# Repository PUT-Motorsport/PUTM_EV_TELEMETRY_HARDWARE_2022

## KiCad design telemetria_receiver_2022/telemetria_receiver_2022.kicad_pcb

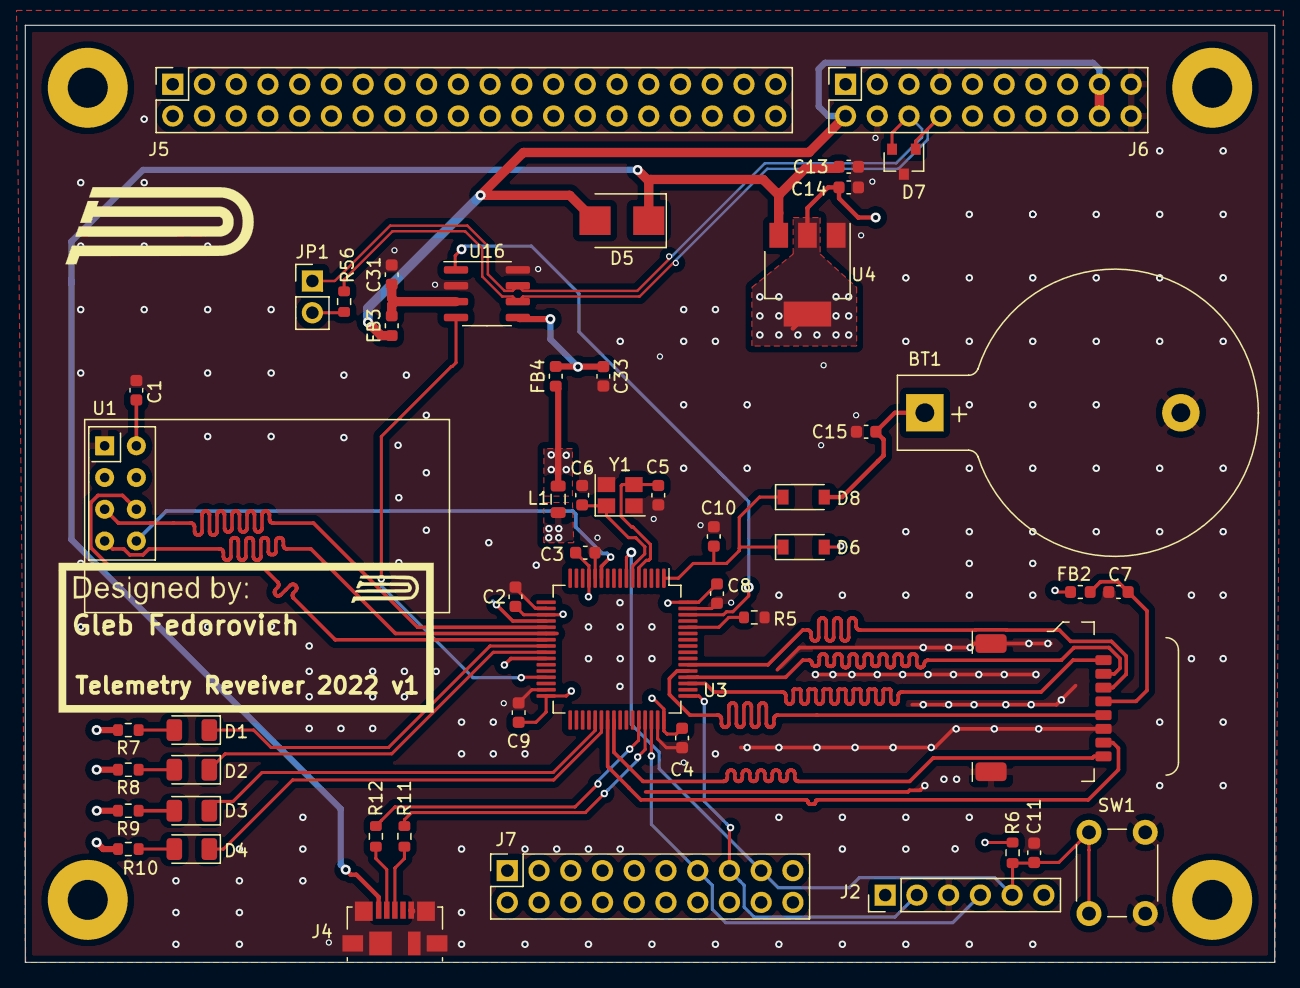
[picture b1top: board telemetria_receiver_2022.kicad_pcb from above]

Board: 4 copper layers, 100.0 x 75.0 mm, 55 parts (0 on the bottom side), 45 nets.

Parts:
BT1: 3V; BatteryHolder_Keystone_103_1x20mm
C1: 10uF; C_0603_1608Metric
C2, C3, C4, C8, C9, C10, C11, C13, C14, C15, C31, C33: 100nF; C_0603_1608Metric
C5, C6: 22pF; C_0603_1608Metric
C7: 4u7F; C_0603_1608Metric
D1, D2, D3, D4: LED; LED_1206_3216Metric
D5: D_Schottky; D_SMB
D6, D8: D_Schottky; D_SOD-123
D7: PESD2CAN.215; SOT-23
FB2, FB3, FB4: 60R@100MHz; L_0603_1608Metric
H1, H2, H3, H4: MountingHole; MountingHole_3.2mm_M3_Pad
J1: Micro_SD_Card; 112K-TAA0-RA1
J2: Conn_01x06_Male; PinHeader_1x06_P2.54mm_Vertical
J4: USB_B_Mini; USB_Micro-B_Molex_47346-0001
J5: Sygnały; PinSocket_2x20_P2.54mm_Vertical
J6: Zasilanie+CAN; PinSocket_2x10_P2.54mm_Vertical
J7: Diagnostyka; PinSocket_2x10_P2.54mm_Vertical
JP1: CAN_termination_jumper; PinHeader_1x02_P2.54mm_Vertical
L1: 10uH; L_0805_2012Metric
R5, R6: 100kR; R_0603_1608Metric
R7, R8, R9, R10: 470R; R_0603_1608Metric
R11, R12: 30R; R_0603_1608Metric
R56: 120R; R_0603_1608Metric
SW1: SW_Push; SW_PUSH_6mm
U1: NRF24L01_Breakout; nRF24L01_Breakout
U3: STM32L4P5RET6; LQFP-64_10x10mm_P0.5mm
U4: LM1117-3.3; SOT-223-3_TabPin2
U16: ATA6561-GAQW-N; SOIC-8_3.9x4.9mm_P1.27mm
Y1: Crystal(100MHZ)?; Crystal_SMD_3225-4Pin_3.2x2.5mm

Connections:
+3V3: C1.1, C14.1, D6.2, FB2.1, FB4.1, J2.1, L1.1, R6.2, R7.2, R8.2, R9.2, R10.2, U1.2, U4.2
+5V: D5.2, FB3.1, J6.2, J6.17, J6.18
+5VD: C13.1, D5.1, J4.1, U4.3
+BATT: BT1.1, C15.2, D8.2
/+3V3_Vbatt: C10.1, D6.1, D8.1, U3.1
/+3V3_uC: C2.1, C3.1, C4.1, C8.1, C9.1, L1.2, U3.13, U3.19, U3.32, U3.48, U3.64
/CAN+: D7.2, J6.6, JP1.1, U16.7
/CAN-: D7.1, J6.8, R56.2, U16.6
/CAN/+3V3_VIO: C33.1, FB4.2, U16.5
/CAN/+5V_CAN_VDD: C31.1, FB3.2, U16.3
/CAN_RX: U3.29, U16.4
/CAN_TX: U3.62, U16.1
/LED_1: D1.1, U3.24
/LED_2: D2.1, U3.25
/LED_3: D3.1, U3.37
/LED_4: D4.1, U3.38
/NRF24_CE: U1.3, U3.26
/NRF24_CSN: U1.4, U3.20
/NRF24_IRQ: U1.8, U3.11
/NRF24_MISO: U1.7, U3.22
/NRF24_MOSI: U1.6, U3.23
/NRF24_SCK: U1.5, U3.21
/NRST: C11.1, J2.5, J7.17, R6.1, SW1.1, U3.7
/SDMMC1_CK: J1.5, U3.53
/SDMMC1_CMD: J1.3, U3.54
/SDMMC1_D0: J1.7, U3.39
/SDMMC1_D1: J1.8, U3.40
/SDMMC1_D2: J1.1, U3.51
/SDMMC1_D3: J1.2, U3.52
/SD_card/+3V3_SD: C7.1, FB2.2, J1.4
/SW_CLK: J2.2, J7.15, U3.49
/SW_DIO: J2.4, J7.13, U3.46
/USB_DM: R12.2, U3.44
/USB_DP: R11.2, U3.45
GND: BT1.2, C1.2, C2.2, C3.2, C4.2, C5.2, C6.2, C7.2, C8.2, C9.2, C10.2, C11.2, C13.2, C14.2, C15.1, C31.2, C33.2, D7.3, J1.6, J1.9, J2.3, J4.5, J4.6, J6.4, J6.7, J6.19, J6.20, R5.2, SW1.2, U1.1, U3.12, U3.18, U3.31, U3.47, U3.63, U4.1, U16.2, U16.8, Y1.2, Y1.4
unnamed: C5.1, U3.5, Y1.3
unnamed: C6.1, U3.6, Y1.1
unnamed: D1.2, R7.1
unnamed: D2.2, R8.1
unnamed: D3.2, R9.1
unnamed: D4.2, R10.1
unnamed: J4.2, R12.1
unnamed: J4.3, R11.1
unnamed: JP1.2, R56.1
unnamed: R5.1, U3.60

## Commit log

2022-01-18 Create HARDWARE
2022-02-23 moved NRF module, added silkscreens
    the NRF module with PA+LNA is longer than assumed
2022-02-27 added logos lib, fixed routing, impedance matching of spi and sdio, removed external RTC, PCB rearrangement
2022-03-04 controlled impedance tracks, added mounting holes
2022-03-05 Added 3d model and logos
2022-03-05 Transmiter placement changed
2022-03-05 led via moved
2022-03-05 Deleted old gerbers
2022-03-05 Gerbers generated
